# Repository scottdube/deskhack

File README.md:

# deskhack

Home Assistant control and height readback for an **ErgoSwiss hydraulic standing
desk** running a **LOGICDATA COMPACT-e-3-VAL-ES-US** control box ("Compact-3-eco",
software V290) — without buying the vendor Memory handset, and without opening
either sealed box.

The desk shipped with a dumb up/down panel: no presets, no display. This project
taps the 7-pin DIN handset cable inline, drives the button lines from an ESP32
through optocouplers, and reads the desk's height from a previously undocumented
serial broadcast the control box sends on one of the handset pins. The original
panel keeps working in parallel.

As far as I can tell this is the first public decode of the COMPACT-e-**3**
handset bus. The well-known reverse-engineering projects
([RoboDesk](https://github.com/phord/RoboDesk),
[logicdata-standing-desk](https://github.com/DanielHabenicht/logicdata-standing-desk))
target the COMPACT-e-2L, whose framing differs in an important way (see below).

## The protocol

Everything below was measured on real hardware with a $12 FX2LP logic analyzer
and `sigrok-cli`; nothing is copied from other models' documentation.

### Physical

7-pin DIN (DIN 45329 family) between handset and control box. Wire colours in
the cheap extension cable used for the tap:

| wire   | function                                              |
|--------|-------------------------------------------------------|
| brown  | GND                                                   |
| red    | +5V supply to handset                                 |
| white  | HS line — assert **high** to drive **UP**             |
| yellow | HS line — assert **high** to drive **DOWN**           |
| green  | HS line, unused by the basic panel (memory functions) |
| blue   | HS line, unused by the basic panel (memory functions) |
| black  | serial data **out of** the box, idles high            |

Button lines are **active-high** and high-impedance: the box's inputs are
sensitive enough that a multimeter in ohms mode will command motion (ask me how
I know). A dumb panel is nothing but switches connecting HS lines to the +5V
rail.

### Serial framing

The data line is **1000 baud, 9 data bits, no parity, 1 stop, LSB-first** — a
classic 9-bit multi-drop bus. Community docs for the COMPACT-e-2L describe
"1000 baud with even parity"; on this box that is a misread of the 9th data
bit. The framing here was solved by constraint propagation over the raw bit
runs (every 0 must sit inside a frame; see `dataline.py` and `messages.py`),
not assumed.

Packets are two 9-bit words, sent only **when the displayed height changes**
(one packet per inch of travel) plus a fixed handshake burst at the start of
any button press. Packet: `0x07F` header, then the payload word.

### Height

```
height_inches = (245 - (payload & 0xFF)) / 2
```

Verified against a tape measure at four points across the full travel
(69–96 cm on this desk, 27.0–38.0 in): every reading within 0.5 cm. The box
counts pump-motor Hall pulses internally, so this is the same position the
controller itself acts on.

### The 8N1 trick

You do not need 9-bit UART support to read this bus — a plain **8N1** UART at
1000 baud recovers every payload byte intact. But how the packet arrives
depends on how the UART handles framing errors, and real ESP32 silicon
differs from the obvious simulation:

- A UART that **discards** error bytes and resyncs bit-by-bit (what a naive
  software decoder does) sees the header mis-frame into a constant `0xFE`
  sync marker followed by the height byte.
- The **ESP32 keeps** framing-error bytes (verified on an ESP32-WROOM-32,
  ESP-IDF 5.5). Packets arrive as `00 7F <payload>`: the header comes through
  verbatim as `0x7F`, each framing error also emits a `0x00` artifact, and
  the payload byte is unmangled.

Either way the sync-then-payload structure survives. On the ESP32: skip
`0x00`, treat `0x7F` as "next byte is payload".

Filtering the handshake burst is easy thanks to an accident of the encoding:
**real heights are always odd bytes** (`245 - 2*inches`), and the handshake
constants are even or outside the travel range — except `0x0BF`, which
aliases a true 27.0 in reading. Its tell is timing: as a handshake word it
arrives within ~400 ms of the others, as a real height it arrives alone, so
reject `0xBF` seen within 600 ms of other handshake traffic. The working
lambda is in `desk.yaml`.

## Hardware

Eight components, all through-hole:

- 2 × PC817 optocoupler (or CPC1017N photoMOS) — GPIO drives the LED through
  330 Ω; the output side connects a button line to the +5V rail, exactly as a
  finger on the panel does
- 2 × 100 kΩ bleed, opto emitter → GND, so leakage can't float the
  high-impedance inputs
- 3 × 22 kΩ — divider (22k : 44k) dropping the 5 V data line to 3.3 V for the
  ESP32's RX
- ESP32 dev board on its own USB supply, grounds tied at the DIN cable

The tap itself is a male-female 7-pin DIN extension cable cut in half and
landed on lever nuts, so the whole thing unplugs back to stock in seconds.

![The tap: a 7-pin DIN extension cut in half, each conductor landed in a
WAGO 221 lever nut with a pigtail out to the logic analyzer](docs/tap.jpeg)

Nothing is soldered and nothing on the desk is modified — the box and the
original panel each keep their own connector, and the lever nuts sit in
between. Pull the two halves and the desk is stock again.

![The injection rig: a cheap male-female 7-pin DIN extension cut in half, both
halves landed in WAGO 221 lever nuts. Male end to the control box, female end
to the original handset.](docs/injection-rig.jpeg)

**This rig is the whole trick, and it generalises.** It is a $10 extension
cable, not the desk's harness. Cutting it gives you seven conductors broken out
into lever nuts, which is simultaneously a **probe point** for the logic
analyzer and an **injection point** for the ESP32 — read the bus and drive it
without ever putting a knife near the cable that came with the machine. Get it
wrong, unplug two connectors, and the desk has never been touched. Any bus
that runs through a detachable cable can be attacked this way.

![The finished board wired to the rig on the bench, before install. The
wire-colour legend along each terminal block matches the DIN conductor
colours.](docs/board-and-rig.jpeg)

The board keeps the same idea: J1 and J4 are wired straight through, so the
control box and the original handset each land on their own terminal block and
the ESP32 sits across the pair. The panel goes on working exactly as before.

### The cable shield is left floating — on purpose

The handset cable is seven conductors **plus a shield**, and the shield is not
grounded here. That is deliberate, and it is worth stating plainly because the
instinct on seeing an ungrounded shield is that somebody forgot.

**It is not grounded in the desk's own wiring.** The two halves of the tap have
their drains joined to each other, so the shield stays electrically continuous
end to end exactly as it was before the cable was cut — and it terminates
nowhere, exactly as it did before.

Why not "improve" it: **the whole design goal is that the control box cannot
tell the difference.** Everything else here is built that way — the original
panel keeps working, the box keeps its own connector, nothing is soldered to
the desk. Bonding the shield to logic ground would be a change to a mains-fed
system whose internal grounding we cannot see, in exchange for a benefit
nothing has demonstrated a need for. If the box grounds the shield at its end,
adding a second bond creates a loop.

No idea *why* LOGICDATA left it floating. Matching what the manufacturer did is
the conservative choice when you do not know the reason.

`kicad/` contains a KiCad 10 project (ERC-clean, footprints assigned) with the
interface circuit and a 30-pin ESP32 DevKit V1 socket, ready for board layout.
The schematic is *generated* — edit `kicad/gen_sch.py` and rerun rather than
editing the sheet, or retire the generator once you start hand-routing.

## Firmware

`desk.yaml` is a complete ESPHome configuration:

- height sensor via the 8N1 trick (hardware UART, zero protocol code)
- target-height number entity + sit/stand/stop buttons for Home Assistant
- bang-bang seek loop (feedback is 1-inch granular; there is nothing finer to
  chase)
- **duty-cycle watchdog** — the box is rated 2 min on / 18 min off and this is
  enforced in firmware, don't remove it; Drive Budget and Budget Recovery
  sensors expose how much motion is left before lockout. The budget persists
  across reboots (and credits real elapsed time while powered off), so an OTA
  can't hand you a fresh one. A diagnostic **Reset Duty Budget** button exists
  for bench work — deliberate operator action only, never automate it
- stall detection (no height change while driving → stop)
- a template **cover** face (0% = bottom of travel, 100% = top) so voice
  assistants can drive it with built-in position intents — no custom
  sentences required, and it provides a voice "stop"

### Voice control: use the cover, not the buttons

The cover face is not a convenience — on Home Assistant it is the *only* part of
this firmware a voice assistant can reach without extra configuration, and that
is worth stating plainly because the sit/stand buttons look like the obvious
target.

HA's local sentence matcher only recognises entities in a fixed set of domains.
Measured against `home-assistant-intents` (en, 851 sentence templates): every
template with a `{name}` slot carries a `requires_context.domain` allow-list, and
the union of every domain any template can target is

    binary_sensor climate cover fan input_boolean lawn_mower light lock
    media_player person scene script sensor switch todo vacuum valve weather

**`button` is not in that set.** So `button.<device>_sit` / `_stand` cannot be
matched by any phrasing — and **entity aliases do not help**, because an alias
only supplies candidate text for a `{name}` slot and there is no `{name}`
template that accepts a button.

What this costs depends on your pipeline. With a purely local assistant, the
buttons are simply unreachable by voice. With an LLM conversation agent and
"prefer handling commands locally" enabled, they still work — but they miss the
local matcher every time and fall through to the LLM, so every "sit"/"stand"
pays a full cloud round trip while `cover` commands answer instantly. That
asymmetry is easy to misread as a problem with the desk, the ESP32 or the WiFi;
it is none of those.

Two ways to get fast sit/stand:

- **Use the cover.** "raise / lower the standing desk" works with no extra
  config. Note the cover's ends are the ends of *travel*, so "lower" goes to the
  bottom of travel, which may be below your preferred sitting height.
- **Add custom sentences** mapping your own phrases to an `intent_script` that
  presses the buttons. This keeps one definition of "sit" and "stand" — in this
  firmware, next to the duty-cycle watchdog — and preserves a non-travel-end
  sitting height.

Copy `wifi.yaml.example` to `wifi.yaml` first.

## Analysis tools

Everything runs on a capture exported to CSV
(`sigrok-cli -i cap.sr -O csv > cap.csv`):

| tool                   | what it does                                                                    |
|------------------------|---------------------------------------------------------------------------------|
| `probe.py`             | per-channel characterization: idle level, edges, implied baud from narrowest pulse |
| `timeline.py`          | button lines as a deglitched state timeline                                     |
| `dataline.py`          | bit-time histogram and exhaustive UART framing search                           |
| `messages.py`          | packet segmentation + solved 9N1 decode — the useful one                        |
| `viewer.py`            | renders a capture as a self-contained interactive HTML waveform viewer          |
| `make_test_capture.py` | synthetic capture for self-testing the toolchain                                |

## Safety notes

- The control box is mains-fed and sealed. Nothing here requires opening it,
  and you shouldn't.
- Disconnect mains before plugging/unplugging anything on the handset cable —
  the box enters a re-commissioning state (down-only until re-homed) if the
  handset connection glitches while powered.
- Respect the 2/18 duty cycle. A "nudge every N minutes" automation will
  overheat the box; preset seeks lasting seconds are fine.
- If the box loses its reference: drive to the bottom, hold both panel buttons
  5 s, drive to the top, hold both 5 s (the §4.2 commissioning procedure — it
  works with a plain up/down panel).

## Applies to

Verified on: ErgoSwiss "Steuerung Compact-3-eco 110V V290" (P/N 124.30290),
LOGICDATA type `COMPACT-e-3-VAL-ES-US`, revision 3/1.9.14, US 120 V. The VAL
firmware is hydraulic-specific ("only for hydraulic lift system — modified
parameters"). Other COMPACT-e-3 variants likely match; measure before you
trust — `probe.py` will tell you in one capture.

## License

MIT. If this saved you a €63 handset or an afternoon with a logic analyzer,
pay it forward.

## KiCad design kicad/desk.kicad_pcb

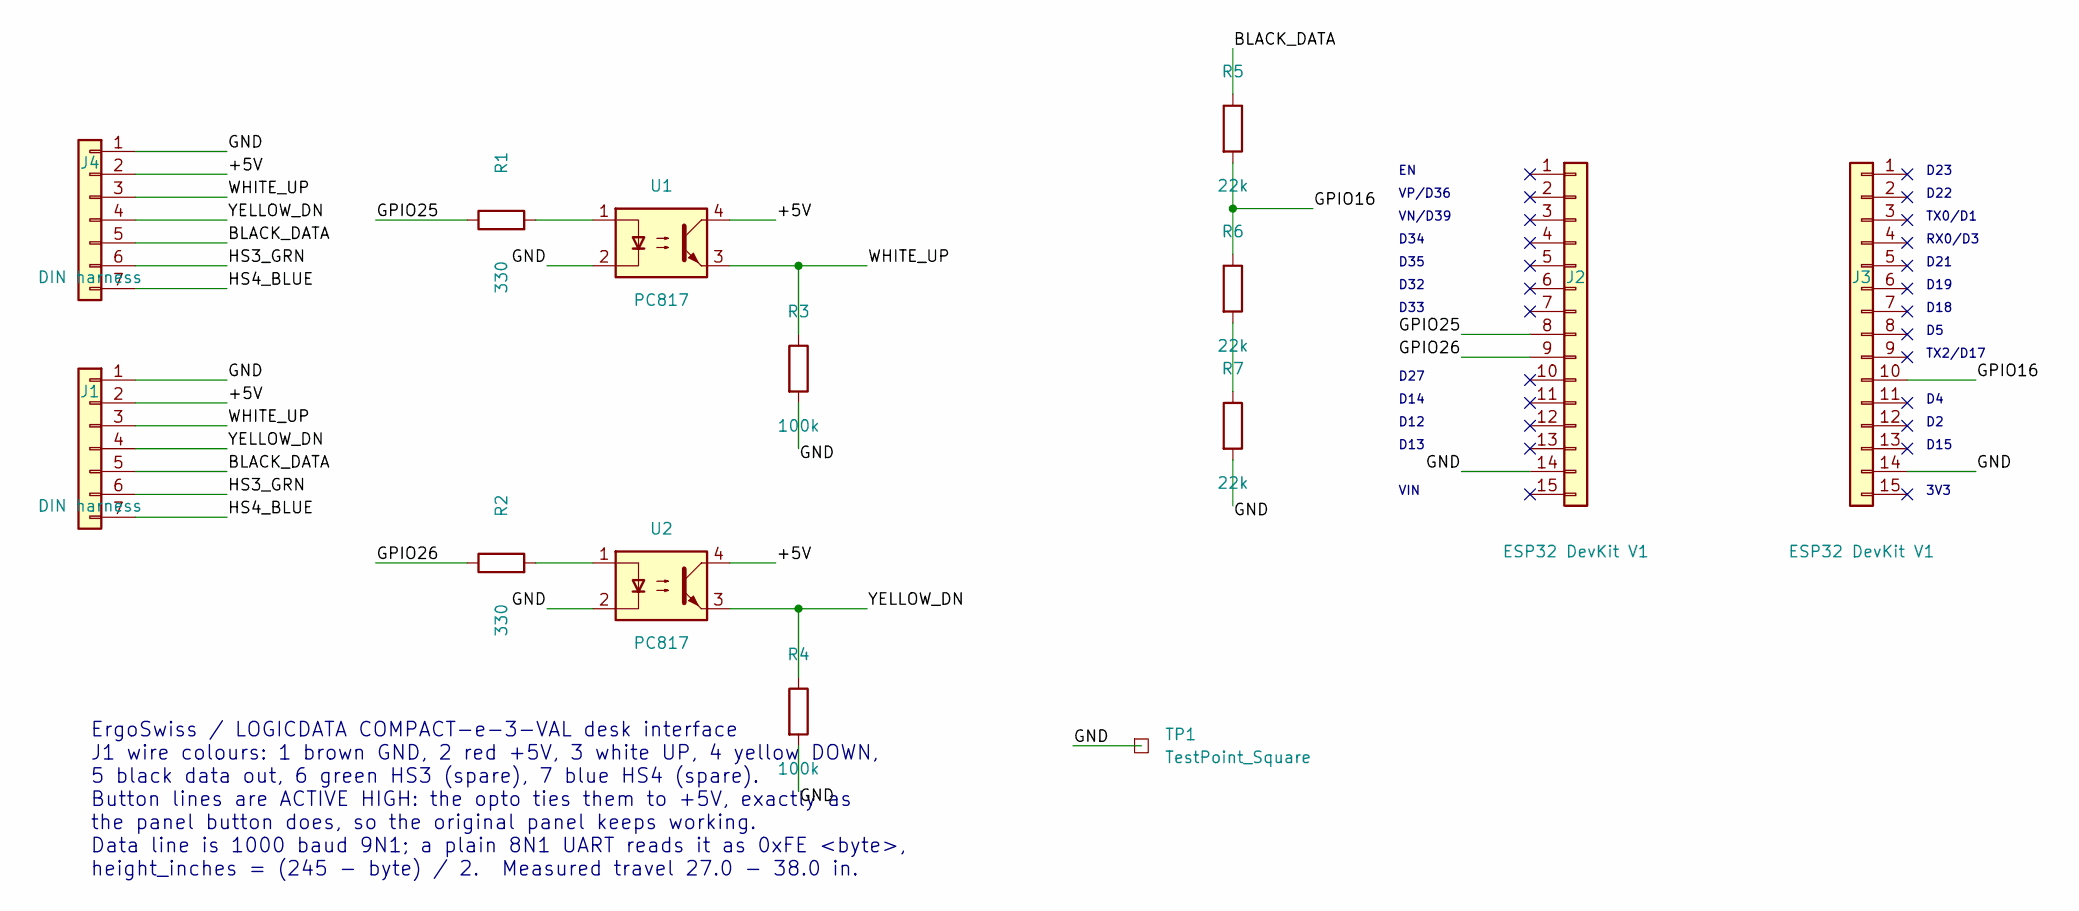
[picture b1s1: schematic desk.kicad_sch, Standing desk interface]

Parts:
J1, J4: DIN harness; TerminalBlock_Phoenix_MKDS-1,5-7_1x07_P5.00mm_Horizontal
J2, J3: ESP32 DevKit V1; PinSocket_1x15_P2.54mm_Vertical
R1, R2: 330; R_Axial_DIN0207_L6.3mm_D2.5mm_P7.62mm_Horizontal
R3, R4: 100k; R_Axial_DIN0207_L6.3mm_D2.5mm_P7.62mm_Horizontal
R5, R6, R7: 22k; R_Axial_DIN0207_L6.3mm_D2.5mm_P7.62mm_Horizontal
TP1: TestPoint_Square; TestPoint_Pad_2.0x2.0mm
U1, U2: PC817; DIP-4_W7.62mm

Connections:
/+5V: J1.2, J4.2, U1.4, U2.4
/BLACK_DATA: J1.5, J4.5, R5.1
/GND: J1.1, J2.14, J3.14, J4.1, R3.2, R4.2, R7.2, TP1.1 (1_1), U1.2, U2.2
/GPIO16: J3.10, R5.2, R6.1
/GPIO25: J2.8, R1.1
/GPIO26: J2.9, R2.1
/HS3_GRN: J1.6, J4.6
/HS4_BLUE: J1.7, J4.7
/WHITE_UP: J1.3, J4.3, R3.1, U1.3
/YELLOW_DN: J1.4, J4.4, R4.1, U2.3
unnamed: R1.2, U1.1
unnamed: R2.2, U2.1
unnamed: R6.2, R7.1

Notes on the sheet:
D12
D35
ErgoSwiss / LOGICDATA COMPACT-e-3-VAL desk interface J1 wire colours: 1 brown GND, 2 red +5V, 3 white UP, 4 yellow DOWN, 5 black data out, 6 green HS3 (spare), 7 blue HS4 (spare). Button lines are ACTIVE HIGH: the opto ties them to +5V, exactly as the panel button does, so the original panel keeps 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
RX0/D3
D33
D19
D18
TX2/D17
D22
3V3
D23
TX0/D1
D32
D14
D15
D21
D34
D13
VP/D36
VN/D39
VIN
D27

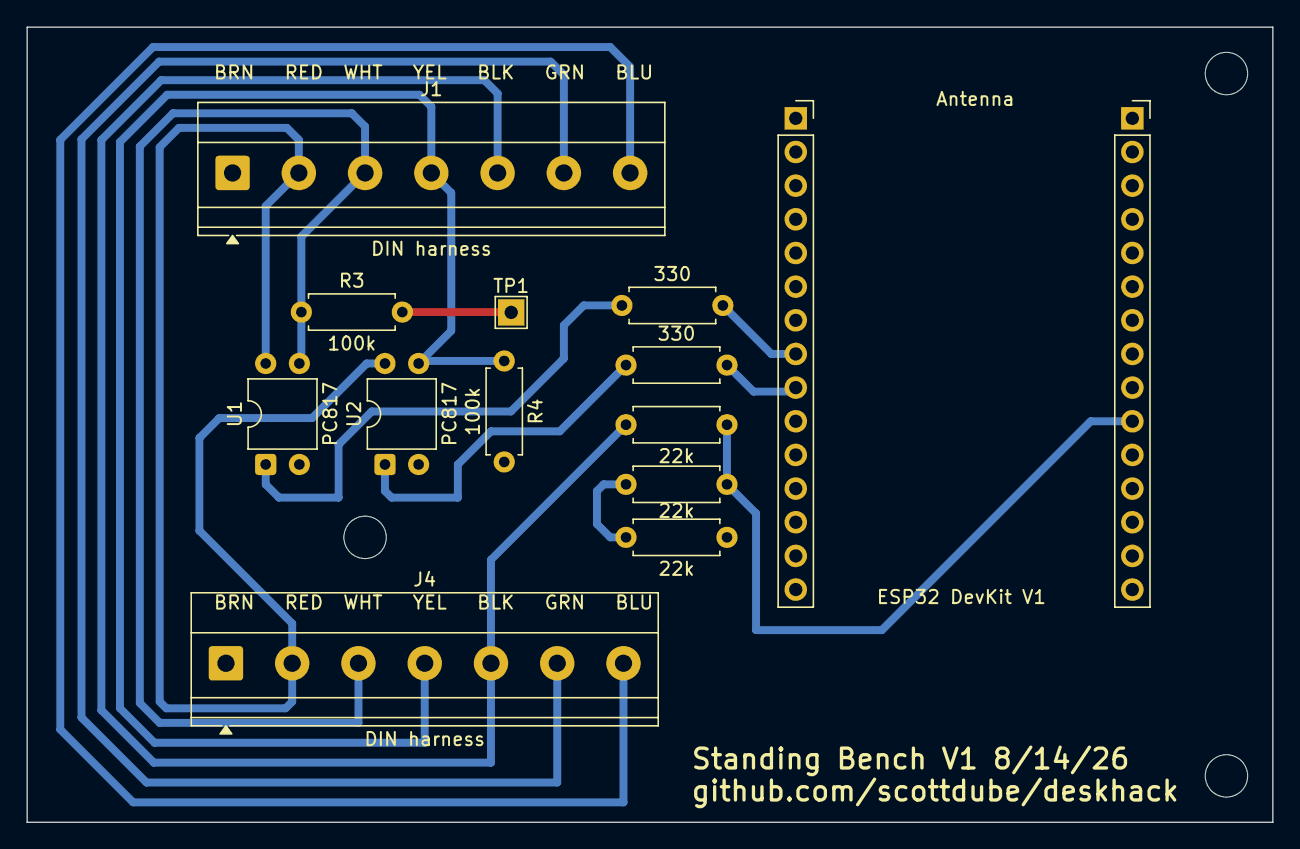
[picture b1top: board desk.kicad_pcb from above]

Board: 2 copper layers, 94.0 x 60.0 mm, 14 parts (0 on the bottom side), 13 nets.

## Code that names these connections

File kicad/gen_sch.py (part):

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
    # ---- opto channels. PC817: 1 anode, 2 cathode, 3 emitter, 4 collector.
    for ref_u, ref_r, ref_b, gpio, net, y in (
        ("U1", "R1", "R3", "GPIO25", "WHITE_UP", 76.2),
        ("U2", "R2", "R4", "GPIO26", "YELLOW_DN", 114.3),
    ):
        r = comp("Device", "R", ref_r, "330", 109.22, y, rot=90,
                 footprint="Resistor_THT:R_Axial_DIN0207_L6.3mm_D2.5mm_P10.16mm_Horizontal")
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
    # ---- 3:1 divider dropping the 5V data line to 3.33V for the ESP32
    x = 190.5
    label("BLACK_DATA", (x, 57.15), justify="left bottom")
    r5 = comp("Device", "R", "R5", "22k", x, 66.04,
              footprint="Resistor_THT:R_Axial_DIN0207_L6.3mm_D2.5mm_P10.16mm_Horizontal")
    r6 = comp("Device", "R", "R6", "22k", x, 83.82,
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    wire(r5["2"], r6["1"])
    junction(tap)
    wire(tap, (x + 15.24, 74.93))
    label("GPIO16", (x + 15.24, 74.93))
    wire(r6["2"], r7["1"])
    wire(r7["2"], (x, 107.95))
    label("GND", (x, 107.95), justify="left top")
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            "D25", "D26", "D27", "D14", "D12", "D13", "GND", "VIN"]
    RIGHT = ["D23", "D22", "TX0/D1", "RX0/D3", "D21", "D19", "D18", "D5",
             "TX2/D17", "RX2/D16", "D4", "D2", "D15", "GND", "3V3"]
    NETS = {"D25": "GPIO25", "D26": "GPIO26", "RX2/D16": "GPIO16",
            "GND": "GND"}
    for ref, x, names, mirror in (("J2", 228.6, LEFT, None),
                                  ("J3", 260.35, RIGHT, "y")):
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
